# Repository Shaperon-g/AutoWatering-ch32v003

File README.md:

# AutoWatering
Простой проект на базе чипа ch32v003j4m6, без HAL, только на регистрах.
Поливалка цветка, использует Arduino модуль влажности почвы и какую-то помпу.

# Управление
На плате есть кнопка, светодиод, и разъемы для датчика влажнности почвы и насоса с дополнительной обвязкой.

При подклюцении питания плата сначала 5 секунд "тупит" (это надо для программирования), а потом моргает один раз светодиодом и проверяет влажность почвы, и если она суше сохраненного значения, то включает помпу на заданное время (по умолчанию 2 секунды, можете изменить в main.cpp:AWTR_WATERING_TIME). 
То же самое МК делает, если быстро нажать кнопку.

Если удержать кнопку на протяжении 2 - 3 секунд, то чип сохраняет значение датчика к себе в flash память в качестве граничного между сухой землей и влажной. После этого должен моргнуть светодиод **дважды**.

Ещё на протяжении всей работы МК отправляет в UART (4800 baudrate) сообщения с информацией, что он сейчас делает.
И если зажать кнопку дольше 5 секунд, то программа уходит в цикл, где передает значение датчика в UART и моргает светодиодом раз в секунду.

# Железо
Собирал я проект из того, что было под ногами, поэтому в моей реализации вы можете увидеть разъём Mini-Jack ля соединения датчика и платы (ну а почему бы и нет). Все компоненты здесь избыточны, поэтому подбирайте что-то своё.

# Сборка
0. Сачала в PATH системы должны быть добавлены папки с GCC от WCH и OpenOCD, или вручную прописать их в 
Makefile (ещё нужен make).
1. Cборка из исходников (если ничего не меняли, то можно пропустить)
    ```
    make build
    ```
2. Подключить WCH-LinkE и прошить.
    ```
    make load
    ```

Если чип уже был прошит этим кодом, то надо успеть в первые 5 секунд его работы. Просто я решил установить очень низкое тактирование, чтобы МК мог находиться в режиме сна более 24 часов, но как оказалось, для SDI нужна частота более 1 мегагерца, поэтому перевод к низкому тактированию происходит спустя 5 секунд. Поэтому же и частота UART должна быть достаточно низкой.

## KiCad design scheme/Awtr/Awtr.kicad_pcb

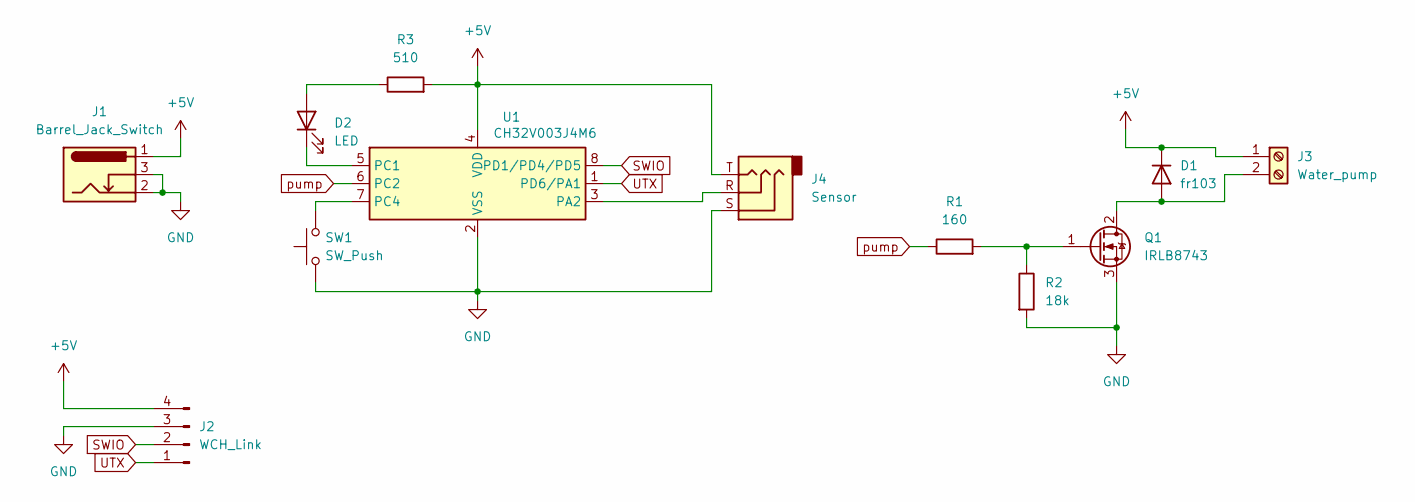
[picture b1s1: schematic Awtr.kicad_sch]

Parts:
D1: fr103; D_DO-41_SOD81_P10.16mm_Horizontal
D2: LED; LED_D5.0mm
J1: Barrel_Jack_Switch; BarrelJack_Horizontal
J2: WCH_Link; PinHeader_1x04_P2.54mm_Vertical
J3: Water_pump; JST_NV_B02P-NV_1x02_P5.00mm_Vertical
J4: Sensor; Jack_3.5mm_CUI_SJ1-3523N_Horizontal
Q1: IRLB8743; TO-220-3_Vertical
R1: 160; R_Axial_DIN0207_L6.3mm_D2.5mm_P10.16mm_Horizontal
R2: 18k; R_0805_2012Metric_Pad1.20x1.40mm_HandSolder
R3: 510; R_0805_2012Metric_Pad1.20x1.40mm_HandSolder
SW1: SW_Push; SW_Push_1TS009xxxx-xxxx-xxxx_6x6x5mm
U1: CH32V003J4M6; SOIC-8_3.9x4.9mm_P1.27mm

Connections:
+5V: D1.1 (K), J1.1, J2.4, J3.1, J4.T, R3.2, U1.4 (VDD)
GND: J1.2, J1.3, J2.3, J4.S, Q1.3 (S), R2.2, SW1.1, U1.2 (VSS); also elsewhere on the board
unnamed: D1.2 (A), J3.2, Q1.2 (D)
unnamed: D2.2 (A), R3.1
unnamed: D2.1 (K), U1.5 (PC1)
unnamed: Q1.1 (G), R1.2, R2.1
unnamed: J4.R, U1.3 (PA2)
unnamed 7: SW1.2, U1.7 (PC4); also elsewhere on the board
SWIO: J2.2, U1.8 (PD1/PD4/PD5)
UTX: J2.1, U1.1 (PD6/PA1)
pump: R1.1, U1.6 (PC2)

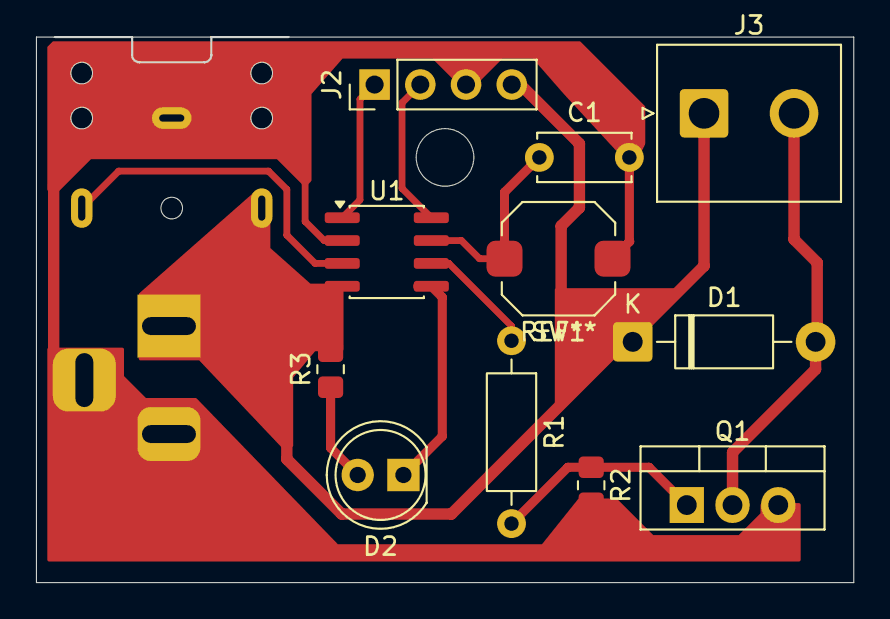
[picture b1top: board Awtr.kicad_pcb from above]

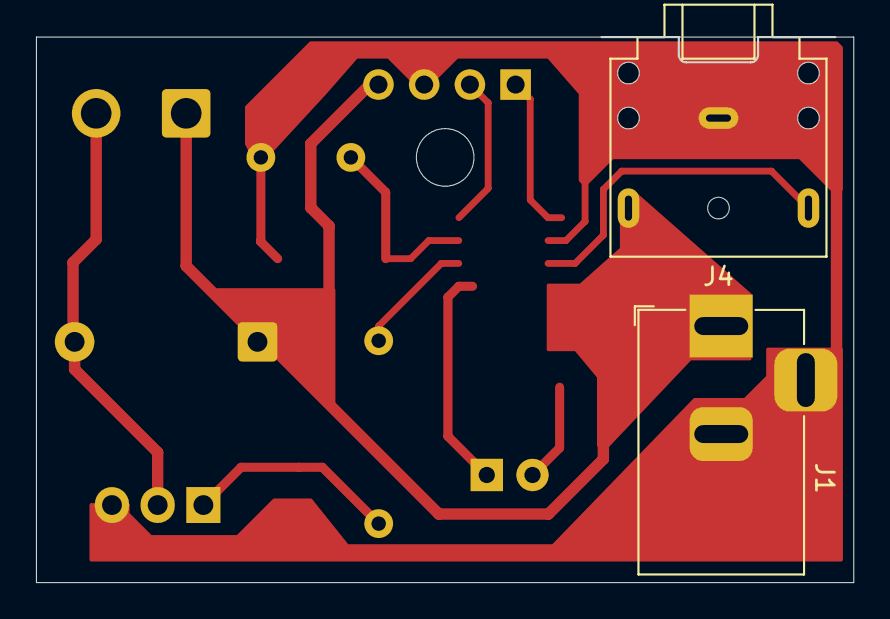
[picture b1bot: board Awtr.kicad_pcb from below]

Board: 2 copper layers, 45.3 x 30.3 mm, 13 parts (2 on the bottom side), 11 nets.

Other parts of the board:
C1: 10pF; C_Disc_D5.0mm_W2.5mm_P5.00mm

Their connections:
GND: C1.2; also elsewhere on the board
unnamed 7: C1.1; also elsewhere on the board

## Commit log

2026-06-26 +saving to flash
2026-06-26 Первый коммит. +tim, btn, uart
2026-06-26 +ADC
2026-06-26 +Sleep mode
2026-06-26 add README
